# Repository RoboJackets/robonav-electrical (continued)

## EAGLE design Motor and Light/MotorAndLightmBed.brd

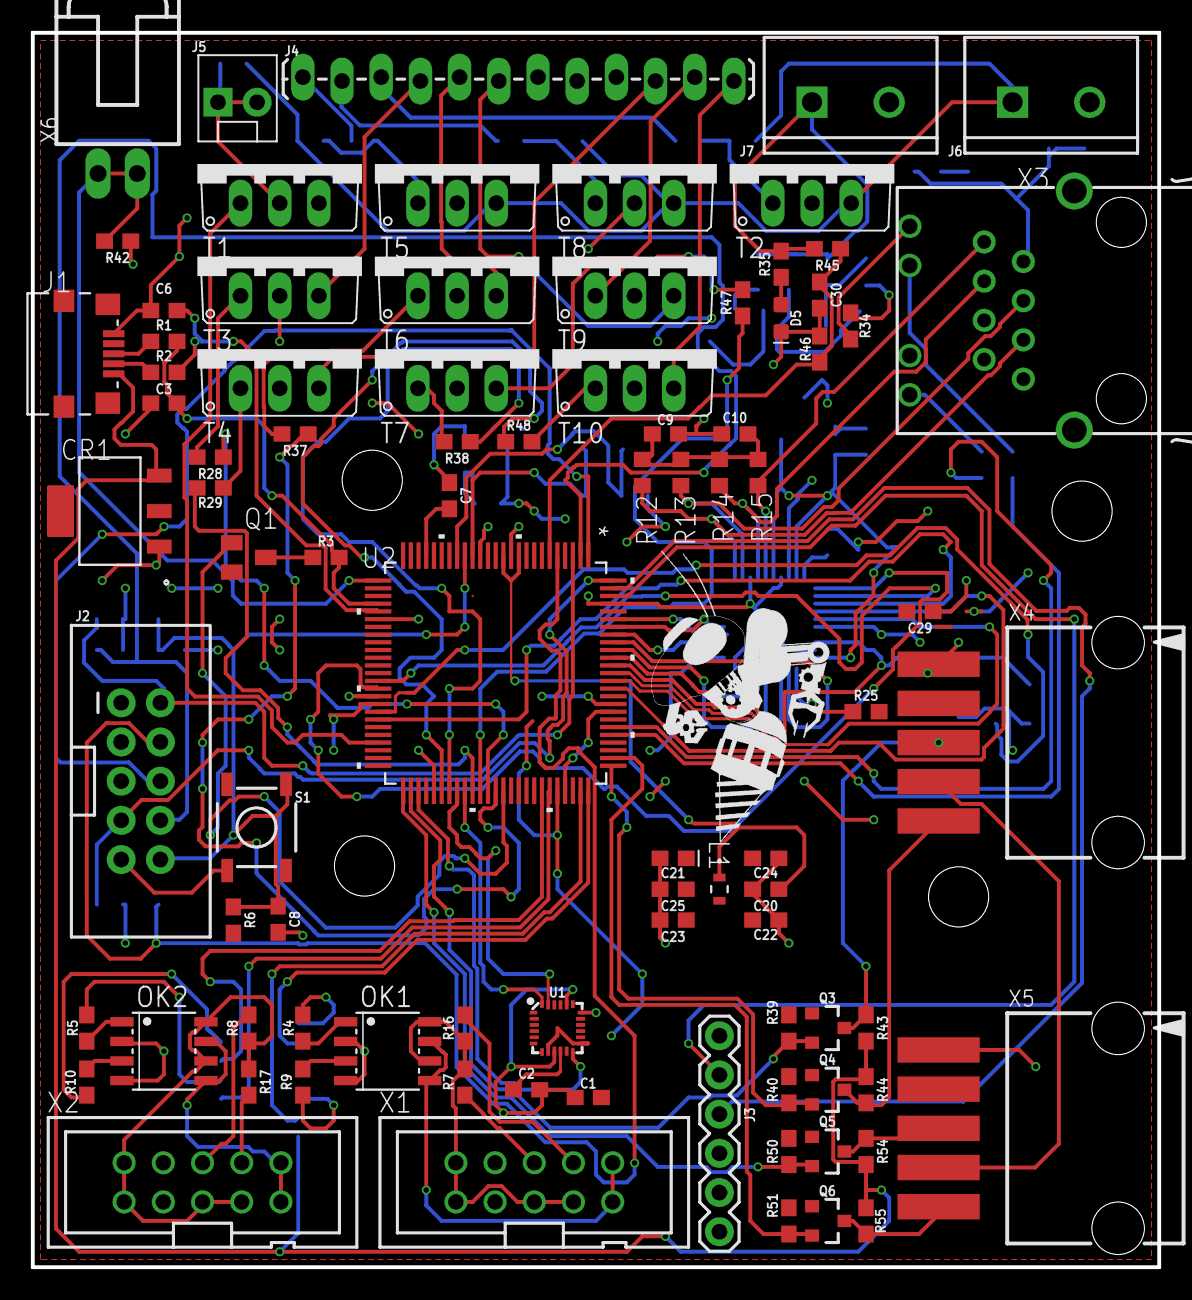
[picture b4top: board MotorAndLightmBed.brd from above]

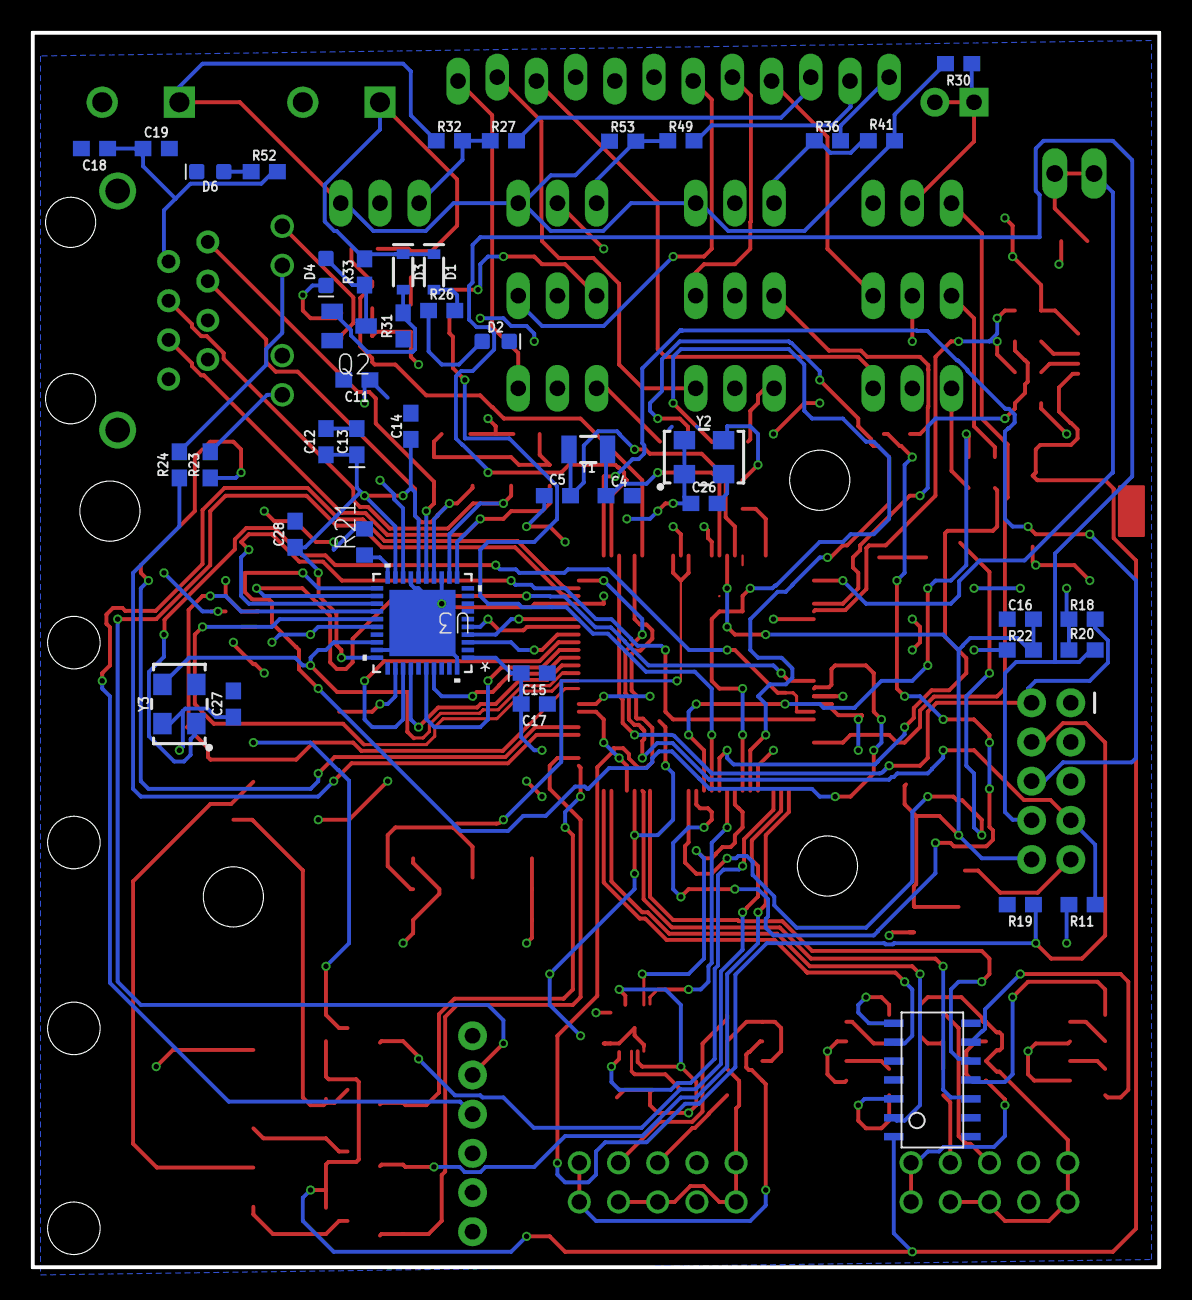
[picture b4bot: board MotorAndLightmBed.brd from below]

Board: 2 copper layers, 73.0 x 80.0 mm, 137 parts (44 on the bottom side), 117 nets.

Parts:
C1, C2, C9, C10, C11, C12, C14, C16, C17, C18, C19, C20, C22, C23, C24, C25, C26, C27, C28, C29, C30: 0.1uF; 0603
C3, C4, C5, C6: 18pF; 0603
C7: 100pF; 0603
C8: 1000pF; 0603
C13, C15, C21: 10uF; 0603-POLAR
CR1: LD1117S33TR; SOT-223
D1, D3: 3.3V; SOD-323
D2: RED; LED-0603
D4: GREEN; LED-0603
D5: BLUE; LED-0603
D6: WHITE; LED-0603
J1: 1981568-1; CONN_1981568-1
J2: Programming Port; 2X5-SHROUDED
J3: 6_PIN_SERIAL_CABLEPTH; FTDI_BASIC
J4: Under Glow; 1X12_LOCK_LONGPADS
J5: Safety Light; MOLEX-1X2
J6: 12V; SCREWTERMINAL-5MM-2
J7: 24V; SCREWTERMINAL-5MM-2
L1: 10uH; IND_1608
OK1, OK2: MOCD208M; SOIC08-FAIRCHILD
Q1: BSS84; SOT23
Q2: BC846ASMD; SOT23
Q3, Q4, Q5, Q6: 220mA/50V/3.5Ω; SOT23-3
R1, R2: 33; 0603
R3: 1.5k; 0603
R4, R5, R9, R10: 1k; 0603
R6: 47k; 0603
R7, R8, R11, R16, R17, R18, R19, R20, R39, R40, R43, R44, R50, R51, R54, R55: 10k; 0603
R12, R13, R14, R15: 49.9; R0603
R21: 4.87k; R0603
R22: 100k; 0603
R23, R24: 150; 0603
R25: 2.2k; 0603
R26, R27, R30, R33, R35, R36, R42, R45, R49, R52: 2700; 0603
R28, R29, R31, R32, R34, R37, R38, R41, R47, R48, R53: 200; 0603
R46: 536; 0603
S1: Momentary Switch 5.2mm; TACTILE_SWITCH_SMD_5.2MM
T1, T2, T3, T4, T5, T6, T7, T8, T9, T10: TIP41A; TO220V
U1: 9DoF IMU; QFN24-3X3
U2: LPC1768FBD100; SOT407-1
U3: DP83848JSQ/NOPB; SQA40B
U$3, U$4, U$5, U$6: STANDOFF-HOLE
U$13: ROBOBUZZ_1.0X
U$14: ICHEXINV; 74HC14
X1, X2: 2510-; PAK100/2500-10
X3: SI-50170
X4, X5: C-GRID-05-15-91; 15-91-05
X6: C-GRID-02-70553; 70553-02
Y1: 32.768kHz; CRYSTAL-SMD-3.2X1.5MM
Y2: OSCILLATORSMD-5X3-12MHz; OSCILLATOR-SMD-5X3.2
Y3: OSCILLATORSMD-5X3-50MHz; OSCILLATOR-SMD-5X3.2

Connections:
1S1: R28.1, U2.62
1S1O: J4.4, T3.3
1S2: R37.1, U2.63
1S2O: J4.5, T6.3
1S3: R47.1, U2.61
1S3O: J4.6, T9.3
2S1: R29.1, U2.60
2S1O: J4.10, T4.3
2S2: R38.1, U2.57
2S2O: J4.11, T7.3
2S3: R48.1, U2.56
2S3O: J4.12, T10.3
12MHZ: C7.1, Y2.3
50MHZ: U2.88, U3.28, Y3.3
!LDIR!: R9.1, U$14.4Y
!LSPEED!: R4.1, U$14.6Y
!RDIR!: R10.1, U$14.3Y
!RSPEED!: R5.1, U$14.2Y
+3V3: C1.1, C9.2, C10.2, C11.1, C15.+, C17.2, C18.1, C19.1, C21.+, C22.1, C23.1, C24.1, C25.1, C26.1, C27.1, C29.2, CR1.2, L1.2, Q1.2, Q3.1, Q4.1, Q5.1, Q6.1, R6.2, R11.2, R12.1, R13.2, R14.1, R15.2, R18.2, R20.1, R22.2, R25.2, R39.2, R40.2, R50.2, R51.2, R52.2, U1.1, U1.8, U1.13, U2.13, U2.19, U2.28, U2.42, U2.54, U2.71, U2.84, U2.96, U3.1, U3.18, U3.26, X3.2, X3.5, Y2.1, Y2.4, Y3.4
+5V: CR1.3, J1.1, R43.2, R44.2, R54.2, R55.2, U$14.VCC
+12V: J6.1, R30.2, R32.2, R41.2, R53.2, T2.3, T5.3, T8.3
+24V: D1.C, D3.C, J7.1, R33.2, R35.2, R45.2
BATTIN: C30.1, R45.1, R46.2, U2.6
BLUE: J4.1, R36.1
ESTOP: R42.2, U2.26, X6.1, X6.2
ETH_LED1: R23.2, X3.A1
ETH_LED2: R24.2, X3.A2
ETH_OSC_EN: U2.43, Y3.1
ETH_RST: U2.44, U3.23
GND: C1.2, C2.2, C3.2, C4.1, C5.1, C6.2, C8.2, C9.1, C10.1, C11.2, C12.2, C13.-, C14.1, C15.-, C16.2, C17.1, C18.2, C19.2, C20.2, C21.-, C22.2, C23.2, C24.2, C25.2, C26.2, C27.2, C28.2, C29.1, C30.2, CR1.1, D2.C, D5.C, D6.C, J1.5, J2.3, J2.5, J2.9, J3.GND, J6.2, J7.2, OK1.2, OK1.4, OK2.2, OK2.4, Q2.2, R19.2, R21.2, R31.1, R34.1, R42.1, R46.1, S1.4, T1.3, T2.2, T3.2, T4.2, T5.2, T6.2, T7.2, T8.2, T9.2, T10.2, U1.9, U1.18, U1.20, U2.11, U2.15, U2.31, U2.41, U2.55, U2.72, U2.83, U2.97, U3.13, U3.17, U3.29, U3.40, U3.41, U$14.GND, X3.C1, X3.C2, X3.S1, X3.S2, X4.1, X5.1, Y2.2, Y3.2
GREEN: J4.2, R49.1
GYRO_INT: U1.12, U2.53
L+12V: OK1.6, OK1.8, R7.2, R16.1, X1.1, X1.2, X1.5, X1.7
LALI: R7.1, X1.6
LBLI: R16.2, X1.8
LDIR: U2.74, U$14.4A
LEA: Q3.3, R43.1, X4.3
LEA3: Q3.2, R39.1, U2.52
LEB: Q4.3, R44.1, X4.5
LEB3: Q4.2, R40.1, U2.76
LED_LINK: U2.39, U3.22
LED_SPEED: U2.40, U3.21
LGND: OK1.5, OK1.7, X1.9, X1.10
LPC_D+: J1.3, R1.1
LPC_D-: J1.2, R2.1
LSPEED: U2.75, U$14.6A
unnamed: OK1.1, R4.2
unnamed: C4.2, U2.16, Y1.P$2
unnamed: C5.2, U2.18, Y1.P$1
unnamed: Q1.3, R3.1
unnamed: OK2.1, R5.2
unnamed: OK2.3, R10.2
unnamed: OK1.3, R9.2
unnamed: C7.2, U2.22
unnamed: R23.1, U2.81
unnamed: C2.1, U1.10
unnamed: R21.1, U3.20
unnamed: R24.1, U2.80
unnamed: R25.1, U3.32
unnamed: J5.1, J5.2, R30.1, T1.2
unnamed: R27.2, R32.1, T2.1
unnamed: R36.2, R41.1, T5.1
unnamed: R49.2, R53.1, T8.1
unnamed: R47.2, T9.1
unnamed: R37.2, T6.1
unnamed: R28.2, T3.1
unnamed: R29.2, T4.1
unnamed: R38.2, T7.1
unnamed: R48.2, T10.1
unnamed: D1.A, R26.2
unnamed: D2.A, R26.1
unnamed: D4.C, R34.2
unnamed: D3.A, Q2.1, R31.2
unnamed: D5.A, R35.1
unnamed: D4.A, Q2.3, R33.1
unnamed: D6.A, R52.1
NRESET: C8.1, C16.1, J2.10, R6.1, R22.1, S1.1, U2.17
PFBOUT: C12.1, C13.+, C14.2, C28.1, U3.16, U3.19, U3.30
R+12V: OK2.6, OK2.8, R8.1, R17.1, X2.1, X2.2, X2.5, X2.7
RALI: R8.2, X2.6
RBLI: R17.2, X2.8
RD+: R13.1, U3.12, X3.4
RD-: R12.2, U3.11, X3.6
RDIR: U2.69, U$14.3A
REA: Q5.3, R54.1, X5.3
REA3: Q5.2, R50.1, U2.51
REB: Q6.3, R55.1, X5.5
REB3: Q6.2, R51.1, U2.77
RED: J4.3, R27.1
RGND: OK2.5, OK2.7, X2.9, X2.10
RSPEED: U2.70, U$14.2A
RTCK: J2.7, R11.1, U2.100
SCL: U1.23, U2.58
SDA: U1.24, U2.59
SLIGHT: T1.1, U2.47
TCLK: J2.4, R19.1, U2.5
TD+: R15.1, U3.15, X3.1
TD-: R14.2, U3.14, X3.3
TDI: J2.8, R20.2, U2.2
TDO: J2.6, U2.1
TGT_P1.0: U2.95, U3.4
TGT_P1.1: U2.94, U3.5
TGT_P1.4: U2.93, U3.3
TGT_P1.8: U2.92, U3.33
TGT_P1.9: U2.91, U3.36
TGT_P1.10: U2.90, U3.37
TGT_P1.14: U2.89, U3.34
TGT_P1.16: U2.87, U3.25
TGT_P1.17: U2.86, U3.24
TGT_RXD: J3.TXO, U2.99
TGT_SCON: Q1.1, U2.64
TGT_TXD: J3.RXI, U2.98
TMS: J2.2, R18.1, U2.3
USB_D+: C3.1, R1.2, R3.2, U2.29
USB_D-: C6.1, R2.2, U2.30
VCC: X4.4, X5.4
VDDA: C20.1, L1.1, U2.10, U2.12

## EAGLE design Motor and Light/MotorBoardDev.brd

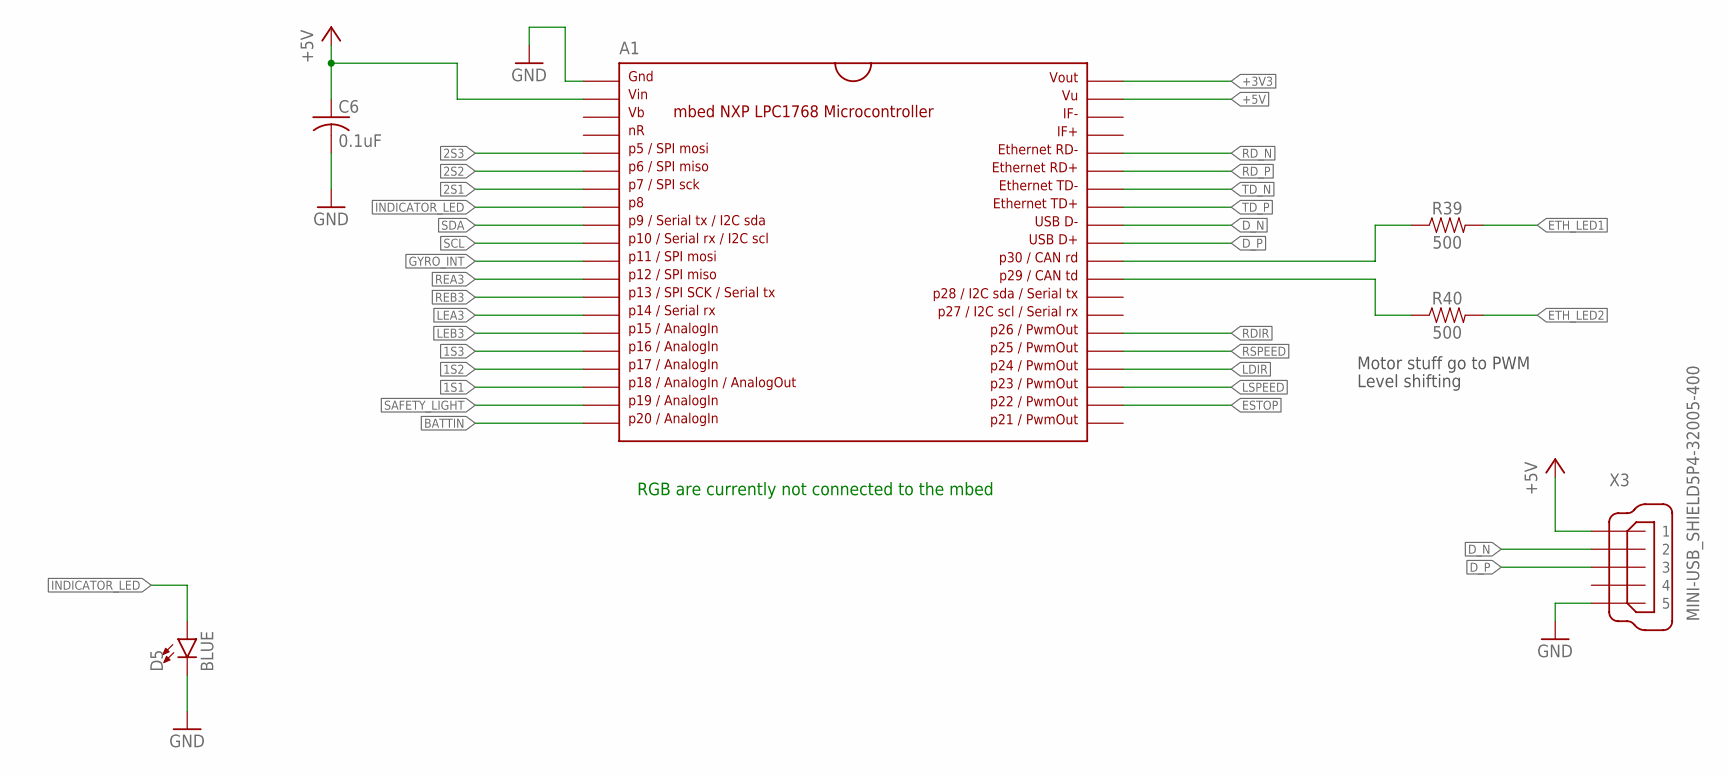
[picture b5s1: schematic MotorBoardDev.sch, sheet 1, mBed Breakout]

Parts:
A1: MBED1768; SPARKFUN-BOARDS_DIL40_0.9
C6: 0.1uF; C0603
D5: BLUE; LED-0603
R39, R40: 500; 0603
X3: MINI-USB_SHIELD5P4-32005-400; 32005-400

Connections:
1S1: A1.18; also elsewhere on the board
1S2: A1.17; also elsewhere on the board
1S3: A1.16; also elsewhere on the board
2S1: A1.7; also elsewhere on the board
2S2: A1.6; also elsewhere on the board
2S3: A1.5; also elsewhere on the board
+3V3: A1.40; also elsewhere on the board
+5V: A1.2, A1.39, C6.1, X3.1; also elsewhere on the board
BATTIN: A1.20; also elsewhere on the board
D_N: A1.32, X3.2
D_P: A1.31, X3.3
ESTOP: A1.22; also elsewhere on the board
ETH_LED1: R39.2; also elsewhere on the board
ETH_LED2: R40.2; also elsewhere on the board
GND: A1.1, C6.2, D5.C, X3.5; also elsewhere on the board
GYRO_INT: A1.11; also elsewhere on the board
INDICATOR_LED: A1.8, D5.A
LDIR: A1.24; also elsewhere on the board
LEA3: A1.14; also elsewhere on the board
LEB3: A1.15; also elsewhere on the board
LSPEED: A1.23; also elsewhere on the board
unnamed: A1.30, R39.1
unnamed: A1.29, R40.1
RDIR: A1.26; also elsewhere on the board
RD_N: A1.36; also elsewhere on the board
RD_P: A1.35; also elsewhere on the board
REA3: A1.12; also elsewhere on the board
REB3: A1.13; also elsewhere on the board
RSPEED: A1.25; also elsewhere on the board
SAFETY_LIGHT: A1.19; also elsewhere on the board
SCL: A1.10; also elsewhere on the board
SDA: A1.9; also elsewhere on the board
TD_N: A1.34; also elsewhere on the board
TD_P: A1.33; also elsewhere on the board

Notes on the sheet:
Motor stuff go to PWM
Level shifting
RGB are currently not connected to the mbed

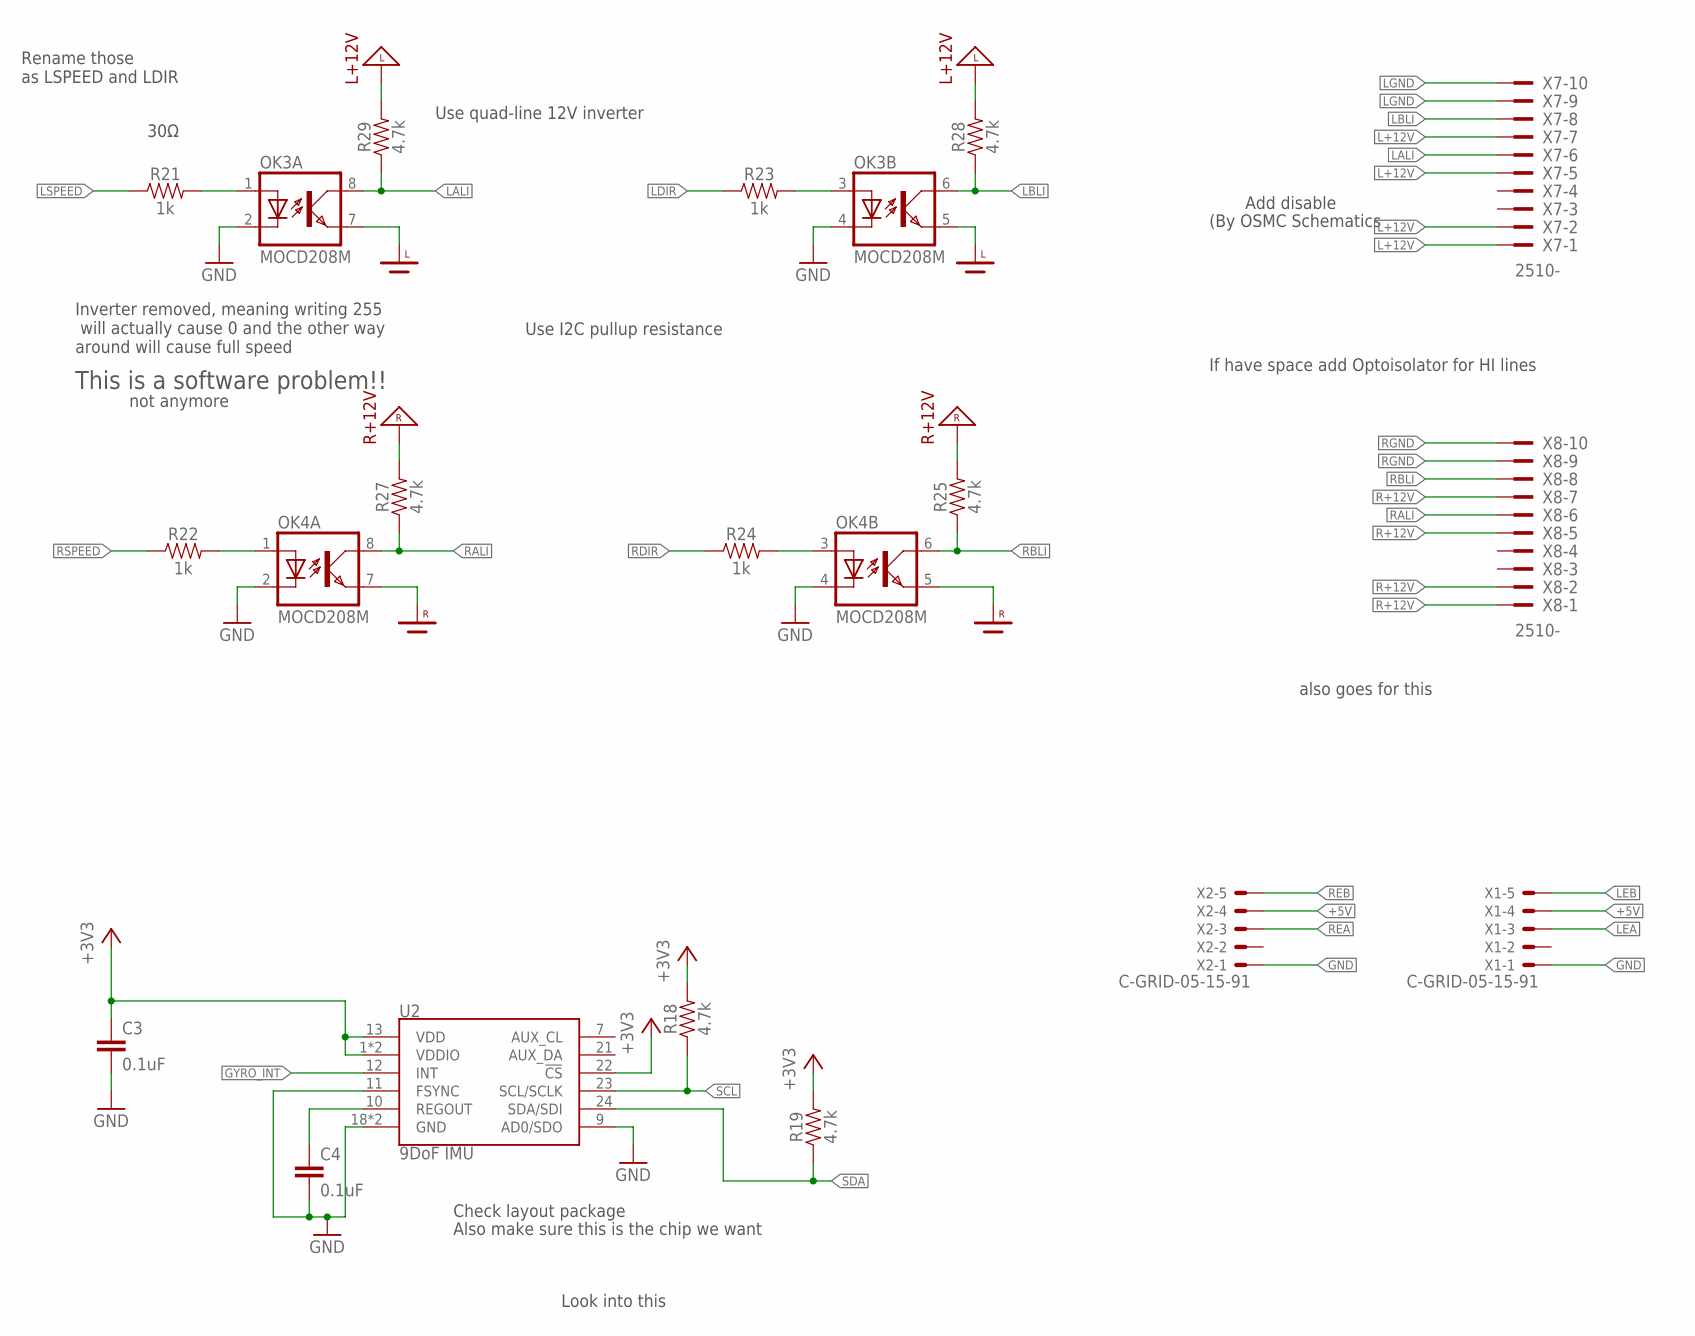
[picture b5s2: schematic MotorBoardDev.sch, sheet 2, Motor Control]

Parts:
C3, C4: 0.1uF; 0603
OK3, OK4: MOCD208M; SOIC08-FAIRCHILD
R18, R19, R25, R27, R28, R29: 4.7k; 0603
R21, R22, R23, R24: 1k; 0603
U2: 9DoF IMU; QFN24-3X3
X1, X2: C-GRID-05-15-91; 15-91-05
X7, X8: 2510-; PAK100/2500-10

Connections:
+3V3: C3.1, R18.2, R19.2, U2.1 (VDDIO), U2.8 (VDDIO), U2.13 (VDD), U2.22 (!CS); also elsewhere on the board
+5V: X1.4, X2.4; also elsewhere on the board
GND: C3.2, C4.2, OK3.2 (C), OK3.4 (C), OK4.2 (C), OK4.4 (C), U2.9 (AD0/SDO), U2.11 (FSYNC), U2.18 (GND), U2.20 (GND), X1.1, X2.1; also elsewhere on the board
GYRO_INT: U2.12 (INT); also elsewhere on the board
L+12V: R28.2, R29.2, X7.1, X7.2, X7.5, X7.7
LALI: OK3.8 (COL), R29.1, X7.6
LBLI: OK3.6 (COL), R28.1, X7.8
LDIR: R23.1; also elsewhere on the board
LEA: X1.3; also elsewhere on the board
LEB: X1.5; also elsewhere on the board
LGND: OK3.5 (EMIT), OK3.7 (EMIT), X7.9, X7.10
LSPEED: R21.1; also elsewhere on the board
unnamed: C4.1, U2.10 (REGOUT)
unnamed: OK3.1 (A), R21.2
unnamed: OK4.1 (A), R22.2
unnamed: OK4.3 (A), R24.2
unnamed: OK3.3 (A), R23.2
R+12V: R25.2, R27.2, X8.1, X8.2, X8.5, X8.7
RALI: OK4.8 (COL), R27.1, X8.6
RBLI: OK4.6 (COL), R25.1, X8.8
RDIR: R24.1; also elsewhere on the board
REA: X2.3; also elsewhere on the board
REB: X2.5; also elsewhere on the board
RGND: OK4.5 (EMIT), OK4.7 (EMIT), X8.9, X8.10
RSPEED: R22.1; also elsewhere on the board
SCL: R18.1, U2.23 (SCL/SCLK); also elsewhere on the board
SDA: R19.1, U2.24 (SDA/SDI); also elsewhere on the board

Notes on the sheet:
Look into this
Inverter removed, meaning writing 255 will actually cause 0 and the other way around will cause full speed
This is a software problem!!
Rename those as LSPEED and LDIR
Use I2C pullup resistance
If have space add Optoisolator for HI lines
Add disable
(By OSMC Schematics
also goes for this
30Ω
Use quad-line 12V inverter
Check layout package
Also make sure this is the chip we want
not anymore

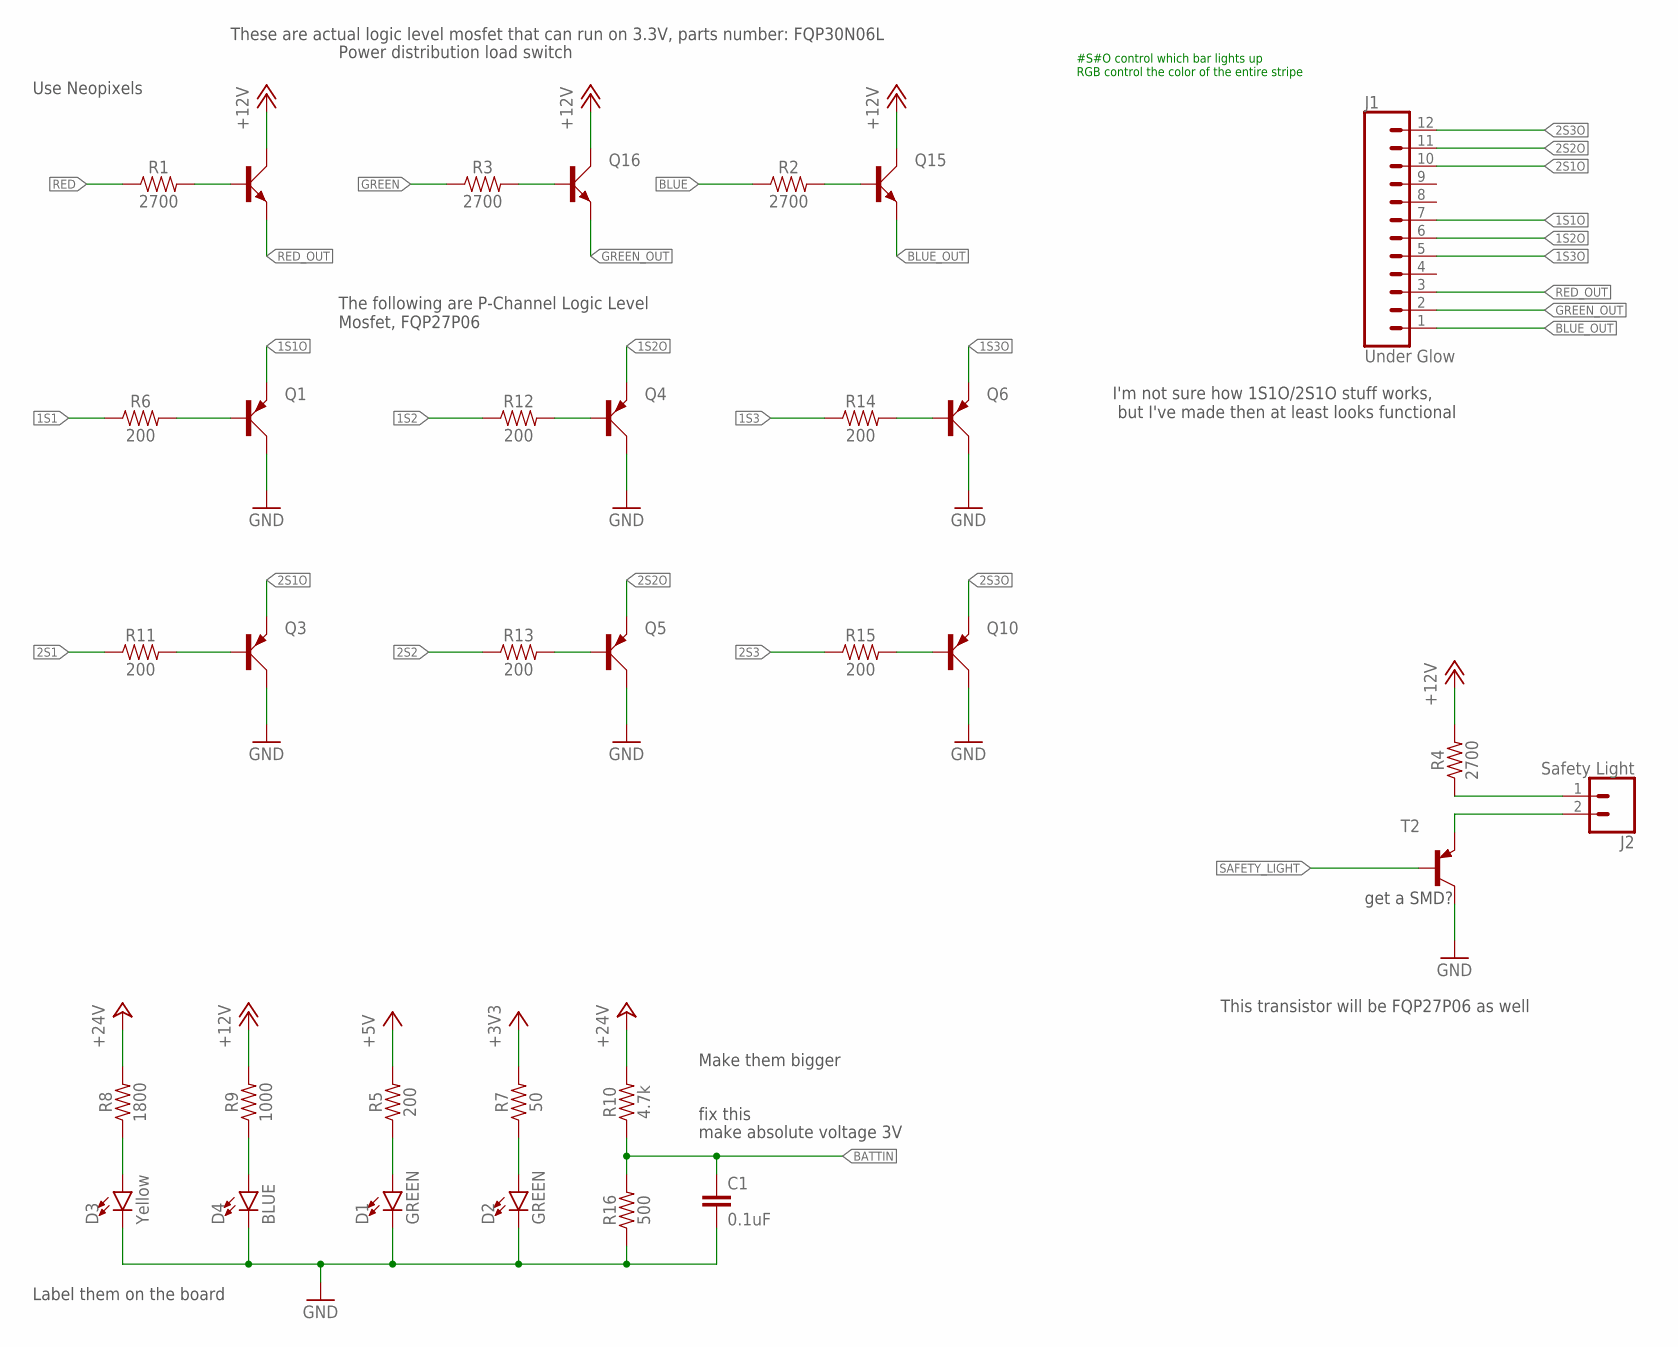
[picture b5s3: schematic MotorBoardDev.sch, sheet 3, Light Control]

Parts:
C1: 0.1uF; 0603
D1, D2: GREEN; LED-0603
D3: Yellow; LED-0603
D4: BLUE; LED-0603
FQP30N06L: TIP41C; TO220AV
J1: Under Glow; 1X12_LOCK_LONGPADS
J2: Safety Light; MOLEX-1X2
Q1, Q3, Q4, Q5, Q6, Q10: TIP42C; TO220AV
Q15, Q16: TIP41C; TO220AV
R1, R2, R3, R4: 2700; 0603
R5, R6, R11, R12, R13, R14, R15: 200; 0603
R7: 50; 0603
R8: 1800; 0603
R9: 1000; 0603
R10: 4.7k; 0603
R16: 500; 0603
T2: TIP41A; TO220V

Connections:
1S1: R6.1; also elsewhere on the board
1S1O: J1.7, Q1.E
1S2: R12.1; also elsewhere on the board
1S2O: J1.6, Q4.E
1S3: R14.1; also elsewhere on the board
1S3O: J1.5, Q6.E
2S1: R11.1; also elsewhere on the board
2S1O: J1.10, Q3.E
2S2: R13.1; also elsewhere on the board
2S2O: J1.11, Q5.E
2S3: R15.1; also elsewhere on the board
2S3O: J1.12, Q10.E
+3V3: R7.2; also elsewhere on the board
+5V: R5.2; also elsewhere on the board
+12V: FQP30N06L.C, Q15.C, Q16.C, R4.2, R9.2; also elsewhere on the board
+24V: R8.2, R10.2; also elsewhere on the board
BATTIN: C1.1, R10.1, R16.2; also elsewhere on the board
BLUE: R2.1
BLUE_OUT: J1.1, Q15.E
GND: C1.2, D1.C, D2.C, D3.C, D4.C, Q1.C, Q3.C, Q4.C, Q5.C, Q6.C, Q10.C, R16.1, T2.2 (C); also elsewhere on the board
GREEN: R3.1
GREEN_OUT: J1.2, Q16.E
unnamed: J2.1, R4.1
unnamed: FQP30N06L.B, R1.2
unnamed: Q15.B, R2.2
unnamed: D1.A, R5.1
unnamed: D2.A, R7.1
unnamed: J2.2, T2.3 (E)
unnamed: D3.A, R8.1
unnamed: Q16.B, R3.2
unnamed: Q6.B, R14.2
unnamed: D4.A, R9.1
unnamed: Q4.B, R12.2
unnamed: Q1.B, R6.2
unnamed: Q3.B, R11.2
unnamed: Q5.B, R13.2
unnamed: Q10.B, R15.2
RED: R1.1
RED_OUT: FQP30N06L.E, J1.3
SAFETY_LIGHT: T2.1 (B); also elsewhere on the board

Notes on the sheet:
These are actual logic level mosfet that can run on 3.3V, parts number: FQP30N06L
The following are P-Channel Logic Level Mosfet, FQP27P06
I'm not sure how 1S1O/2S1O stuff works, but I've made then at least looks functional
This transistor will be FQP27P06 as well
Use Neopixels
Label them on the board
Make them bigger
fix this
make absolute voltage 3V
get a SMD?
Power distribution load switch
#S#O control which bar lights up RGB control the color of the entire stripe

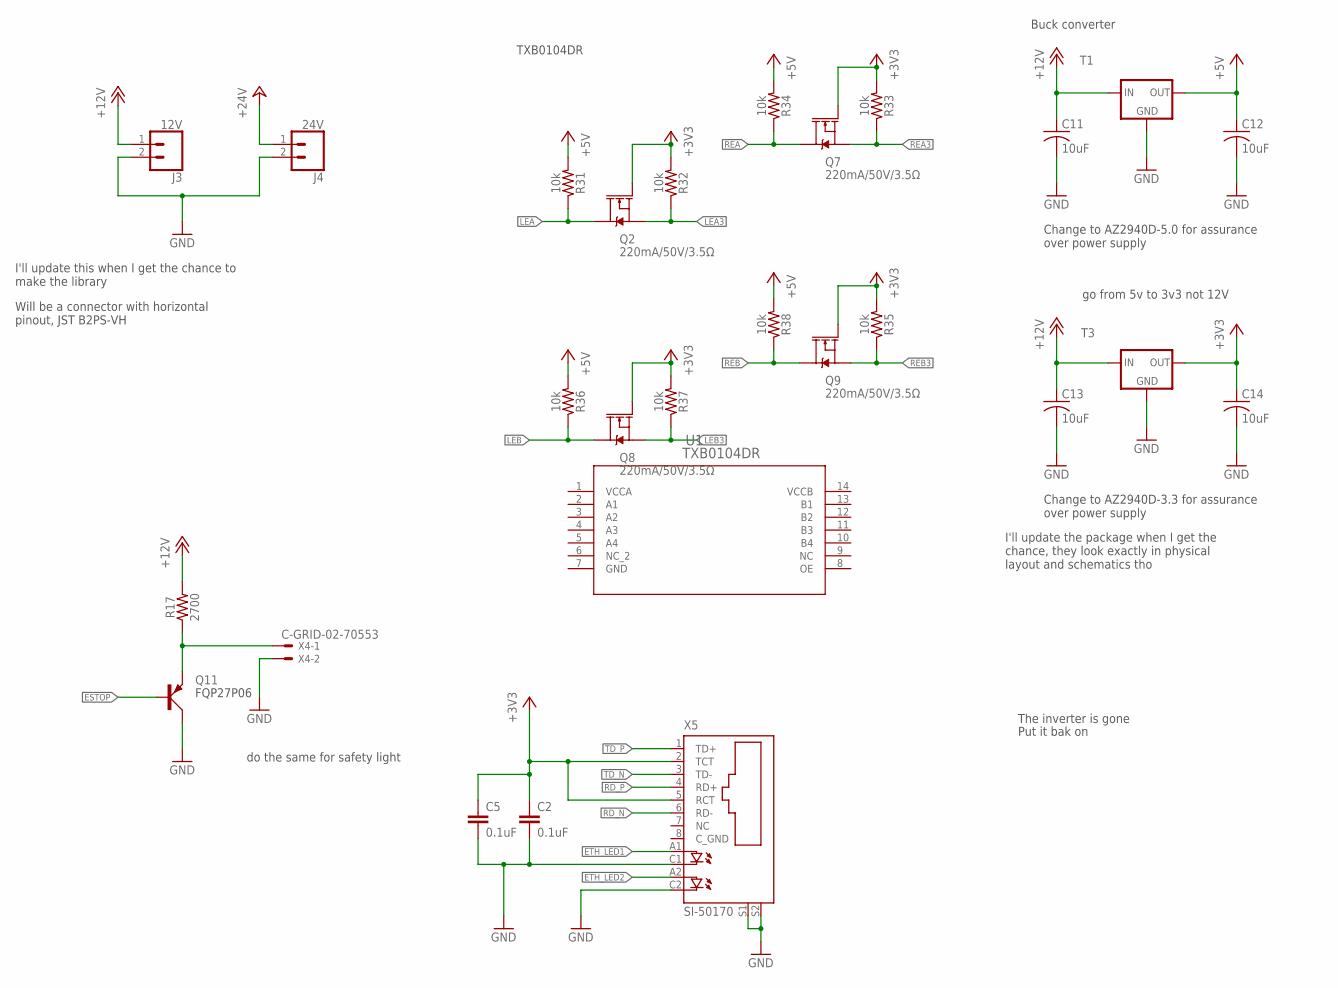
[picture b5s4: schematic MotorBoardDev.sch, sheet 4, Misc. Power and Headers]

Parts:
C2, C5: 0.1uF; 0603
C11, C12, C13, C14: 10uF; C0805
J3: 12V; SCREWTERMINAL-5MM-2
J4: 24V; SCREWTERMINAL-5MM-2
Q2, Q7, Q8, Q9: 220mA/50V/3.5Ω; SOT23-3
Q11: TIP42C; TO220AV
R17: 2700; 0603
R31, R32, R33, R34, R35, R36, R37, R38: 10k; 0603
T1: NCP1117DT50GOS-ND; TO252
T3: NCP1117DT33GOS-ND; TO252
U1: TXB0104DR; D14
X4: C-GRID-02-70553; 70553-02
X5: SI-50170

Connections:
+3V3: C2.1, C5.1, C14.1, Q2.1 (G), Q7.1 (G), Q8.1 (G), Q9.1 (G), R32.2, R33.2, R35.2, R37.2, T3.2 (OUT), X5.2 (TCT), X5.5 (RCT); also elsewhere on the board
+5V: C12.1, R31.2, R34.2, R36.2, R38.2, T1.2 (OUT); also elsewhere on the board
+12V: C11.1, C13.1, J3.1, R17.2, T1.3 (IN), T3.3 (IN); also elsewhere on the board
+24V: J4.1; also elsewhere on the board
ESTOP: Q11.B; also elsewhere on the board
ETH_LED1: X5.A1 (A); also elsewhere on the board
ETH_LED2: X5.A2 (A1); also elsewhere on the board
GND: C2.2, C5.2, C11.2, C12.2, C13.2, C14.2, J3.2, J4.2, Q11.C, T1.1 (GND), T3.1 (GND), U1.7 (GND), X4.2, X5.C1 (C), X5.C2 (C1), X5.S1, X5.S2; also elsewhere on the board
LEA: Q2.3 (D), R31.1; also elsewhere on the board
LEA3: Q2.2 (S), R32.1; also elsewhere on the board
LEB: Q8.3 (D), R36.1; also elsewhere on the board
LEB3: Q8.2 (S), R37.1; also elsewhere on the board
unnamed: Q11.E, R17.1, X4.1
RD_N: X5.6 (RD-); also elsewhere on the board
RD_P: X5.4 (RD+); also elsewhere on the board
REA: Q7.3 (D), R34.1; also elsewhere on the board
REA3: Q7.2 (S), R33.1; also elsewhere on the board
REB: Q9.3 (D), R38.1; also elsewhere on the board
REB3: Q9.2 (S), R35.1; also elsewhere on the board
TD_N: X5.3 (TD-); also elsewhere on the board
TD_P: X5.1 (TD+); also elsewhere on the board
VCCA: U1.1 (VCCA)
VCCB: U1.14 (VCCB)

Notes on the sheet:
I'll update this when I get the chance to make the library
Will be a connector with horizontal pinout, JST B2PS-VH
The inverter is gone
FQP27P06
Change to AZ2940D-5.0 for assurance over power supply
Change to AZ2940D-3.3 for assurance over power supply
I'll update the package when I get the chance, they look exactly in physical layout and schematics tho
Put it bak on
TXB0104DR
do the same for safety light
go from 5v to 3v3 not 12V
Buck converter

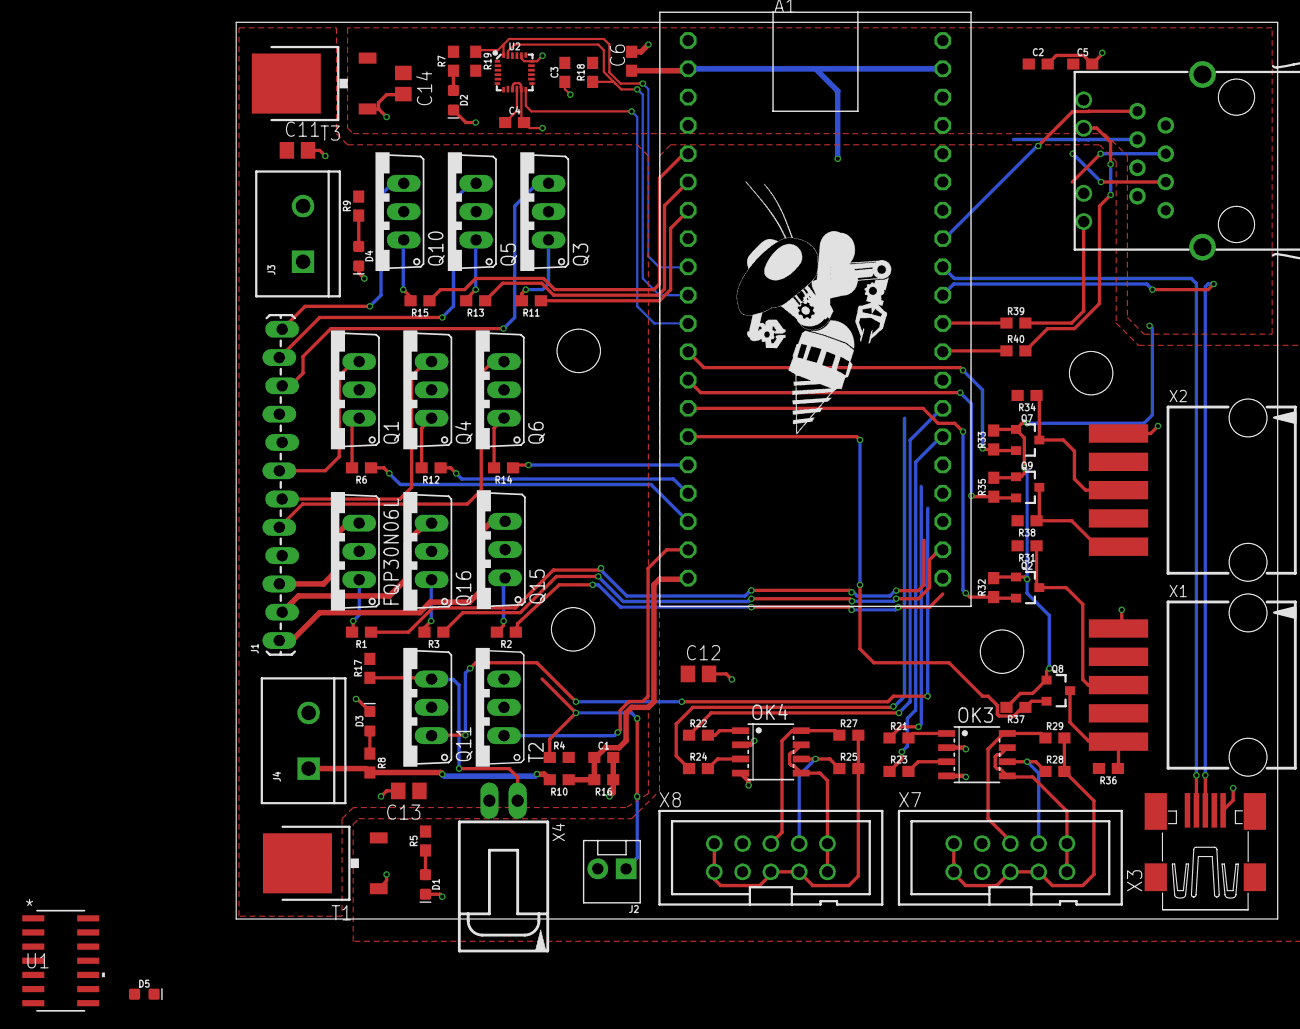
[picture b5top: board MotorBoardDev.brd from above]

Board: 2 copper layers, 93.5 x 80.5 mm, 90 parts (0 on the bottom side), 78 nets.

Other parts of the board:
U$1, U$2, U$3, U$4: STANDOFF-HOLE
U$5: ROBOBUZZ_1.2X

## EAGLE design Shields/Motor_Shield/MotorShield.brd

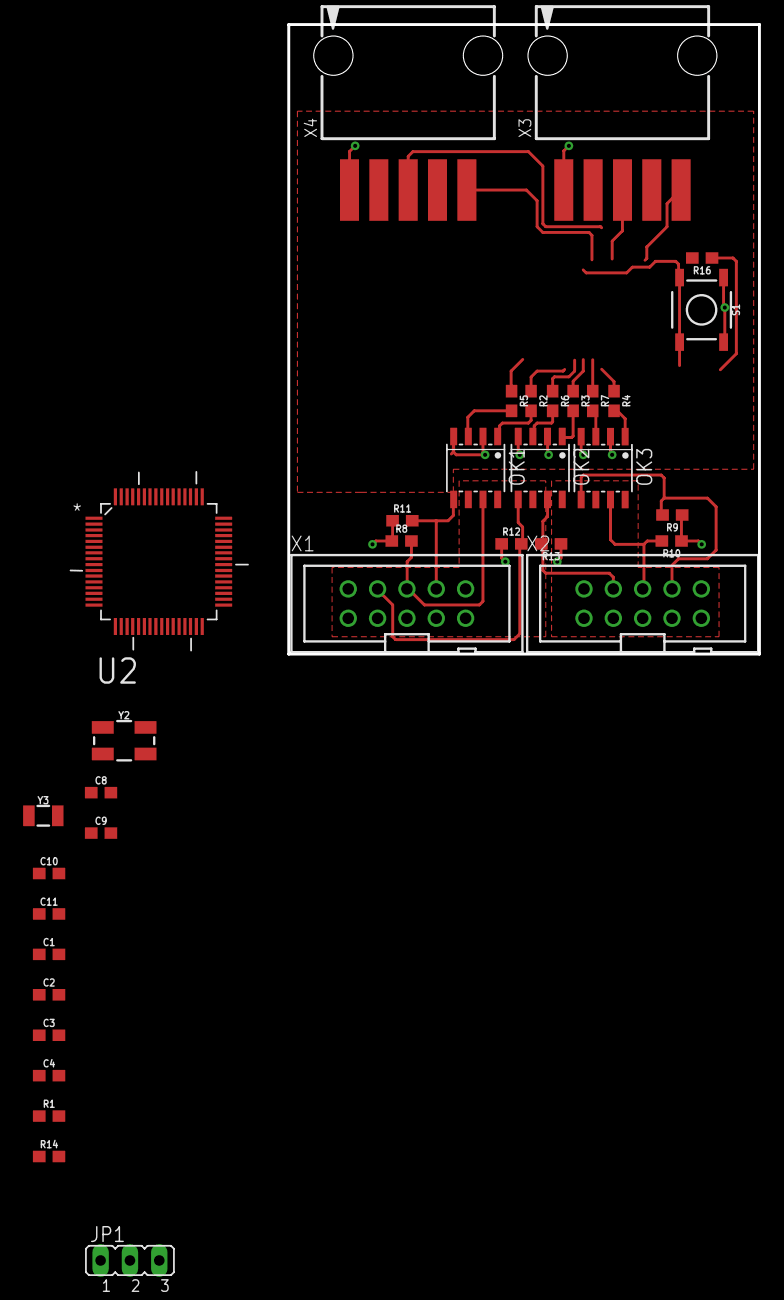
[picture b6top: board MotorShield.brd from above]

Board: 2 copper layers, 40.8 x 54.5 mm, 35 parts (0 on the bottom side), 28 nets.

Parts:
C1, C2, C3, C4: 0.1uF; 0603
C8, C9: 27pF; 0603
C10, C11: 10pF; 0603
JP1: JP2
OK1, OK2, OK3: MOCD208M; SOIC08-FAIRCHILD
R1, R8, R9, R10, R11, R14, R16: 10k; 0603
R2, R3, R4, R5, R6, R7, R12, R13: 1k; 0603
S1: button; TACTILE_SWITCH_SMD_5.2MM
U2: STM32F103RBT6; QFP50P1200X1200X160-64N
X1, X2: 2510-; PAK100/2500-10
X3, X4: C-GRID-05-15-91; 15-91-05
Y2: 8MHz; CRYSTAL-SMD-5X3.2-4PAD
Y3: 32.768kHz; CRYSTAL-SMD-3.2X1.5MM

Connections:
+3.3V: C1.1, C2.1, C3.1, C4.1, U2.1, U2.13, U2.19, U2.32, U2.48, U2.64
+5V: JP1.1, R1.2, R14.2
GND: C1.2, C2.2, C3.2, C4.2, C8.2, C9.2, C10.2, C11.2, JP1.3, OK1.2, OK1.4, OK2.2, OK2.4, OK3.2, OK3.4, S1.1, S1.2, U2.12, U2.18, U2.31, U2.47, U2.63, X3.1, X4.1
LALI: OK1.7, R8.2, X1.6
LBLI: OK1.5, R11.2, X1.8
LDISABLE: OK2.5, R12.2, X1.4
LGND: R8.1, R11.1, R12.1, X1.9, X1.10
LVCC: OK1.6, OK1.8, OK2.6, X1.1, X1.2, X1.5, X1.7
unnamed: OK1.1, R2.2
unnamed: JP1.2, U2.60
unnamed: OK2.1, R3.2
unnamed: OK3.1, R4.2
unnamed: OK3.3, R7.2
unnamed: OK2.3, R6.2
unnamed: OK1.3, R5.2
unnamed: C8.1, U2.5, Y2.3
unnamed: C9.1, U2.6, Y2.1
unnamed: C11.1, U2.4, Y3.P$1
unnamed: C10.1, U2.3, Y3.P$2
RALI: OK3.7, R10.2, X2.6
RBLI: OK3.5, R9.2, X2.8
RDISABLE: OK2.7, R13.2, X2.4
RESET: R16.1, S1.3, S1.4, U2.7
RGND: R9.1, R10.1, R13.1, X2.9, X2.10
RVCC: OK2.8, OK3.6, OK3.8, X2.1, X2.2, X2.5, X2.7
SCL: R14.1, U2.29
SDA: R1.1, U2.30
VCC: R16.2, X3.4, X4.4
